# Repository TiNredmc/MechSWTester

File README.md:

# MechSWTester
Test Cherry MX switch with 0805 led illuminate when press SW

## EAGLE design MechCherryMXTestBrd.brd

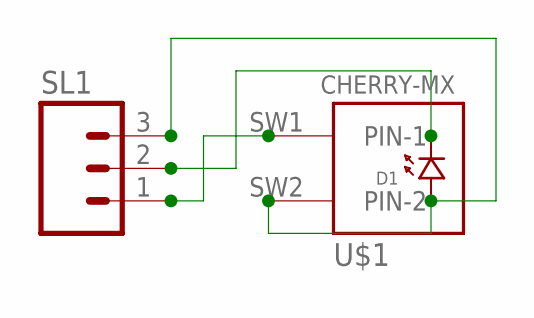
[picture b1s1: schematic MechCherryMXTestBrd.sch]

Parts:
D1: LED.0805; 0805.LED
SL1: M03; 03P
U$1: CHERRY-MX

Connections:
unnamed: D1.P$1 (1), SL1.3, U$1.SW2 (PIN-2)
unnamed: SL1.1, U$1.SW1 (PIN-1)
unnamed: D1.P$2 (2), SL1.2

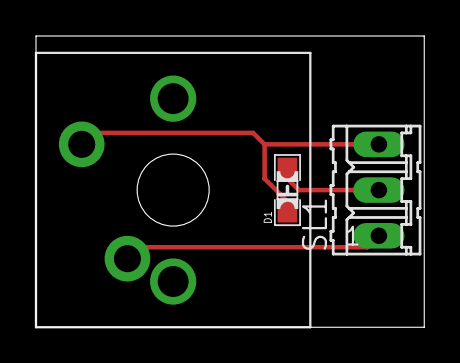
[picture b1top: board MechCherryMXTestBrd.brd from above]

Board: 2 copper layers, 21.6 x 16.2 mm, 3 parts (0 on the bottom side), 3 nets.

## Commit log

2018-02-14 Schematic and board file
